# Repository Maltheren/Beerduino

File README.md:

# Beerduino
A functional arduino uno with a build in bottle opener.

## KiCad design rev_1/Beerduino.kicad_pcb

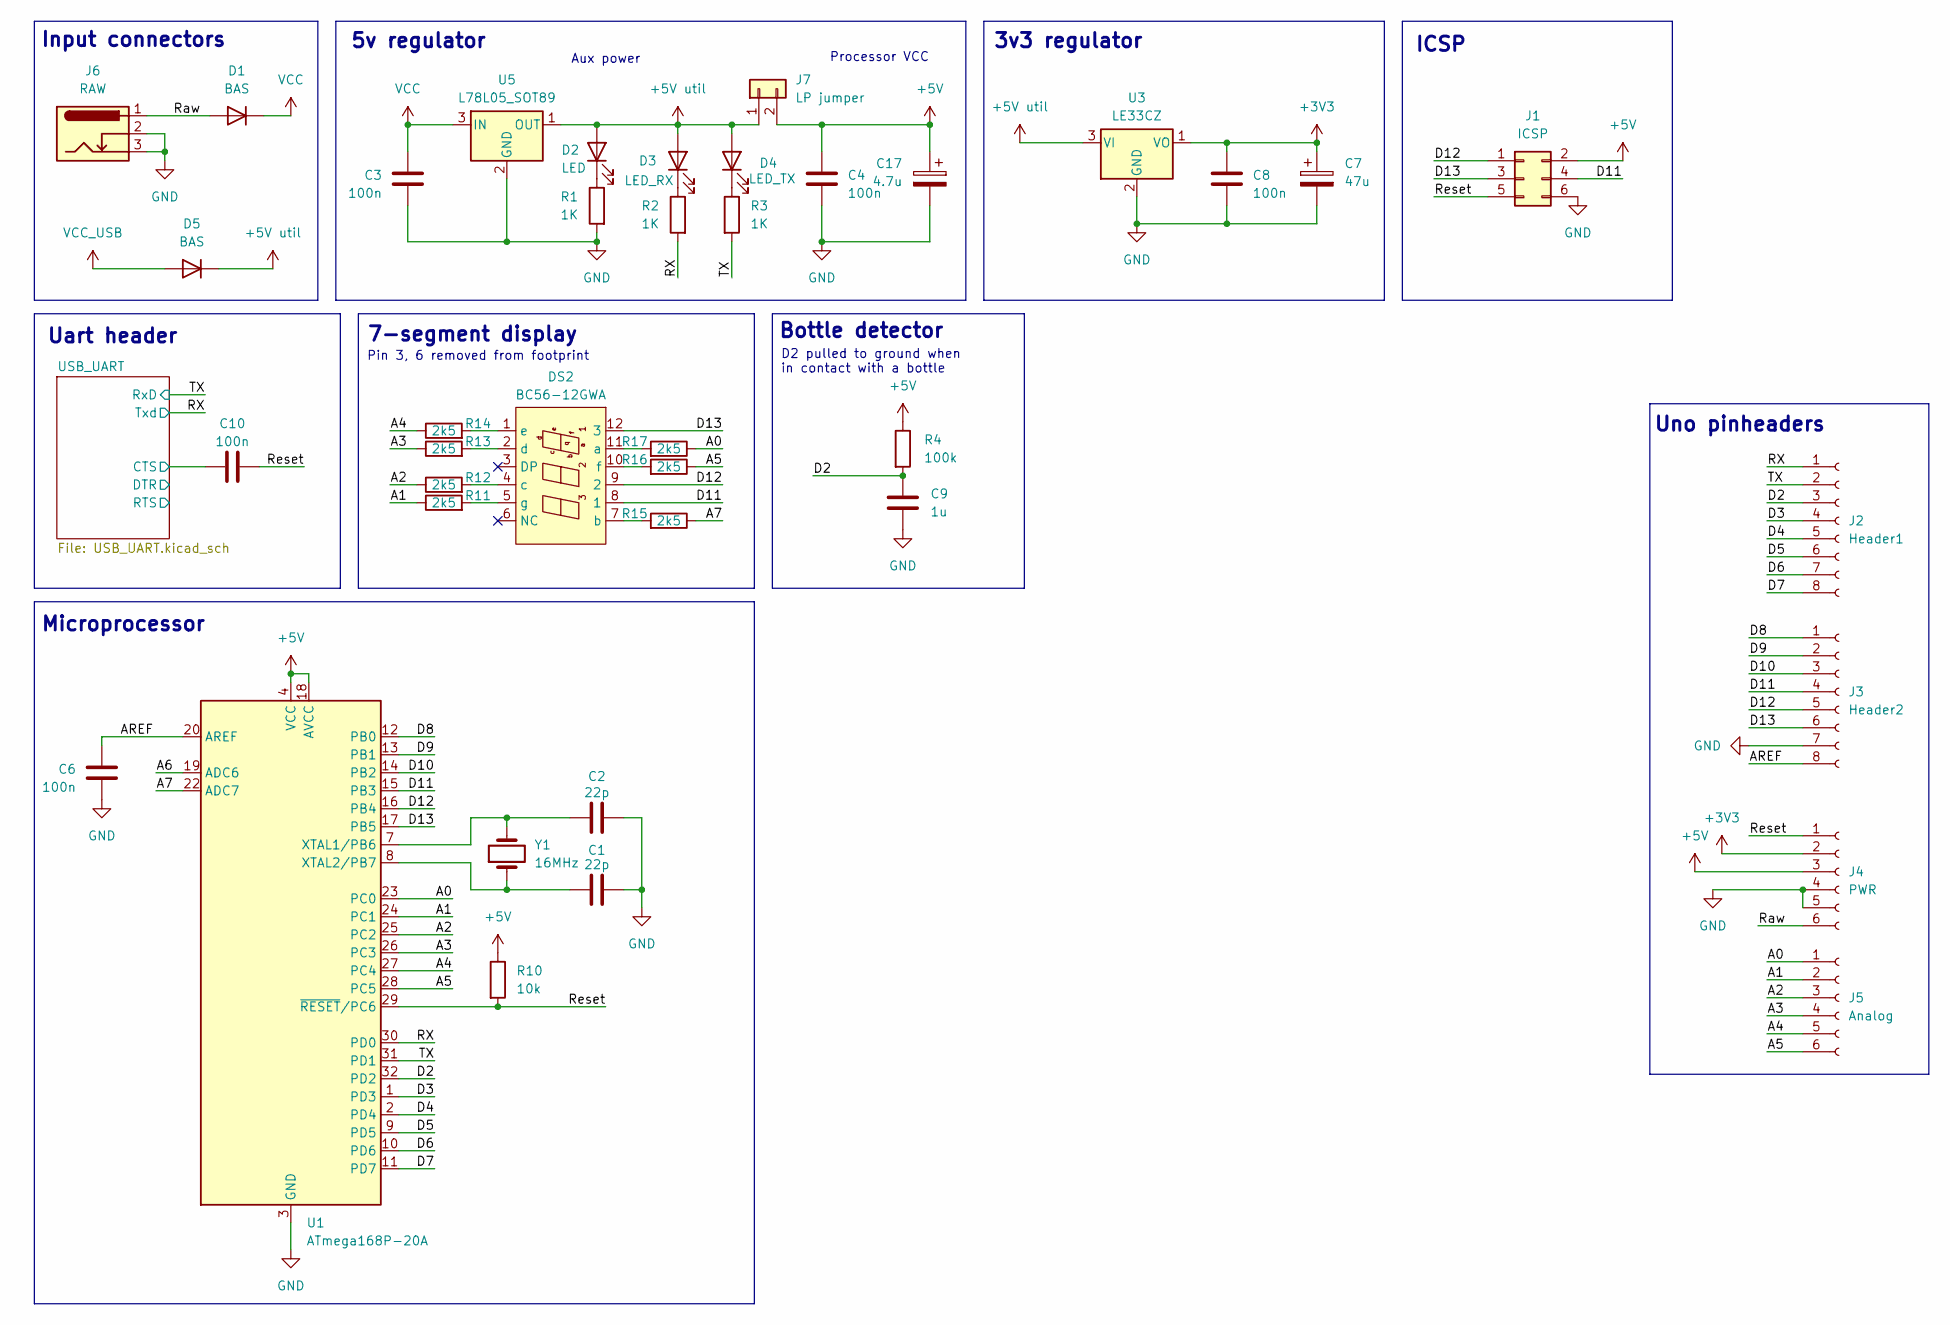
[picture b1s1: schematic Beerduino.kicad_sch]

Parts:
C1, C2: 22p; C_0603_1608Metric_Pad1.08x0.95mm_HandSolder
C3, C4, C6, C8, C10: 100n; C_0603_1608Metric_Pad1.08x0.95mm_HandSolder
C7: 47u; CP_Radial_D5.0mm_P2.50mm
C9: 1u; C_0603_1608Metric_Pad1.08x0.95mm_HandSolder
C17: 4.7u; CP_EIA-3528-15_AVX-H_HandSolder
D1, D5: BAS; D_SOD-323_HandSoldering
D2: LED; LED_0805_2012Metric_Pad1.15x1.40mm_HandSolder
D3: LED_RX; LED_0805_2012Metric_Pad1.15x1.40mm_HandSolder
D4: LED_TX; LED_0805_2012Metric_Pad1.15x1.40mm_HandSolder
DS2: BC56-12GWA; 3digit
J1: ICSP; PinHeader_2x03_P2.54mm_Vertical
J2: Header1; PinSocket_1x08_P2.54mm_Vertical
J3: Header2; PinSocket_1x08_P2.54mm_Vertical
J4: PWR; PinHeader_1x06_P2.54mm_Vertical
J5: Analog; PinHeader_1x06_P2.54mm_Vertical
J6: RAW; BarrelJack_Horizontal
J7: LP jumper; PinHeader_1x02_P2.54mm_Vertical
R1, R2, R3: 1K; R_0603_1608Metric_Pad0.98x0.95mm_HandSolder
R4: 100k; R_0603_1608Metric_Pad0.98x0.95mm_HandSolder
R10: 10k; R_0603_1608Metric_Pad0.98x0.95mm_HandSolder
R11, R12, R13, R14, R15, R16, R17: 2k5; R_0603_1608Metric_Pad0.98x0.95mm_HandSolder
U1: ATmega168P-20A; TQFP-32_7x7mm_P0.8mm
U3: LE33CZ; TO-92_HandSolder
U5: L78L05_SOT89; SOT-89-3
Y1: 16MHz; Crystal_SMD_HC49-SD

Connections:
+3V3: C7.1, C8.1, J4.2, U3.1 (VO)
+5V: C4.1, C17.1, J1.2, J4.3, J7.2, R4.1, R10.1, U1.4 (VCC), U1.6 (VCC), U1.18 (AVCC)
+5V util: D2.2 (A), D3.2 (A), D4.2 (A), D5.1 (K), J7.1, U3.3 (VI), U5.1 (OUT)
/A0: J5.1, R17.1, U1.23 (PC0)
/A1: J5.2, R11.1, U1.24 (PC1)
/A2: J5.3, R12.1, U1.25 (PC2)
/A3: J5.4, R13.1, U1.26 (PC3)
/A4: J5.5, R14.1, U1.27 (PC4)
/A5: J5.6, R16.1, U1.28 (PC5)
/A6: U1.19 (ADC6)
/A7: R15.1, U1.22 (ADC7)
/AREF: C6.1, J3.8, U1.20 (AREF)
/D2: C9.1, J2.3, R4.2, U1.32 (PD2)
/D3: J2.4, U1.1 (PD3)
/D4: J2.5, U1.2 (PD4)
/D5: J2.6, U1.9 (PD5)
/D6: J2.7, U1.10 (PD6)
/D7: J2.8, U1.11 (PD7)
/D8: J3.1, U1.12 (PB0)
/D9: J3.2, U1.13 (PB1)
/D10: J3.3, U1.14 (PB2)
/D11: DS2.8 (1), J1.4, J3.4, U1.15 (PB3)
/D12: DS2.9 (2), J1.1, J3.5, U1.16 (PB4)
/D13: DS2.12 (3), J1.3, J3.6, U1.17 (PB5)
/RX: J2.1, R2.2, U1.30 (PD0); also elsewhere on the board
/Raw: D1.2 (A), J4.6, J6.1
/Reset: C10.1, J1.5, J4.1, R10.2, U1.29 (~RESET/PC6)
/TX: J2.2, R3.2, U1.31 (PD1); also elsewhere on the board
/USB_UART/CTS: C10.2; also elsewhere on the board
GND: C1.2, C2.2, C3.2, C4.2, C6.2, C7.2, C8.2, C9.2, C17.2, J1.6, J3.7, J4.4, J4.5, J6.2, J6.3, R1.2, U1.3 (GND), U1.5 (GND), U1.21 (GND), U3.2 (GND), U5.2 (GND); also elsewhere on the board
unnamed: D2.1 (K), R1.1
unnamed: D3.1 (K), R2.1
unnamed: D4.1 (K), R3.1
unnamed: DS2.11 (a), R17.2
unnamed: DS2.7 (b), R15.2
unnamed: DS2.4 (c), R12.2
unnamed: DS2.2 (d), R13.2
unnamed: DS2.1 (e), R14.2
unnamed: DS2.10 (f), R16.2
unnamed: DS2.5 (g), R11.2
unnamed: C2.1, U1.7 (XTAL1/PB6), Y1.2
unnamed: C1.1, U1.8 (XTAL2/PB7), Y1.1
VCC: C3.1, D1.1 (K), U5.3 (IN)
VCC_USB: D5.2 (A); also elsewhere on the board

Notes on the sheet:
Aux power
Pin 3, 6 removed from footprint
Microprocessor
3v3 regulator
Uart header
Bottle detector
5v regulator
ICSP
Uno pinheaders
Processor VCC
7-segment display
Input connectors
D2 pulled to ground when in contact with a bottle

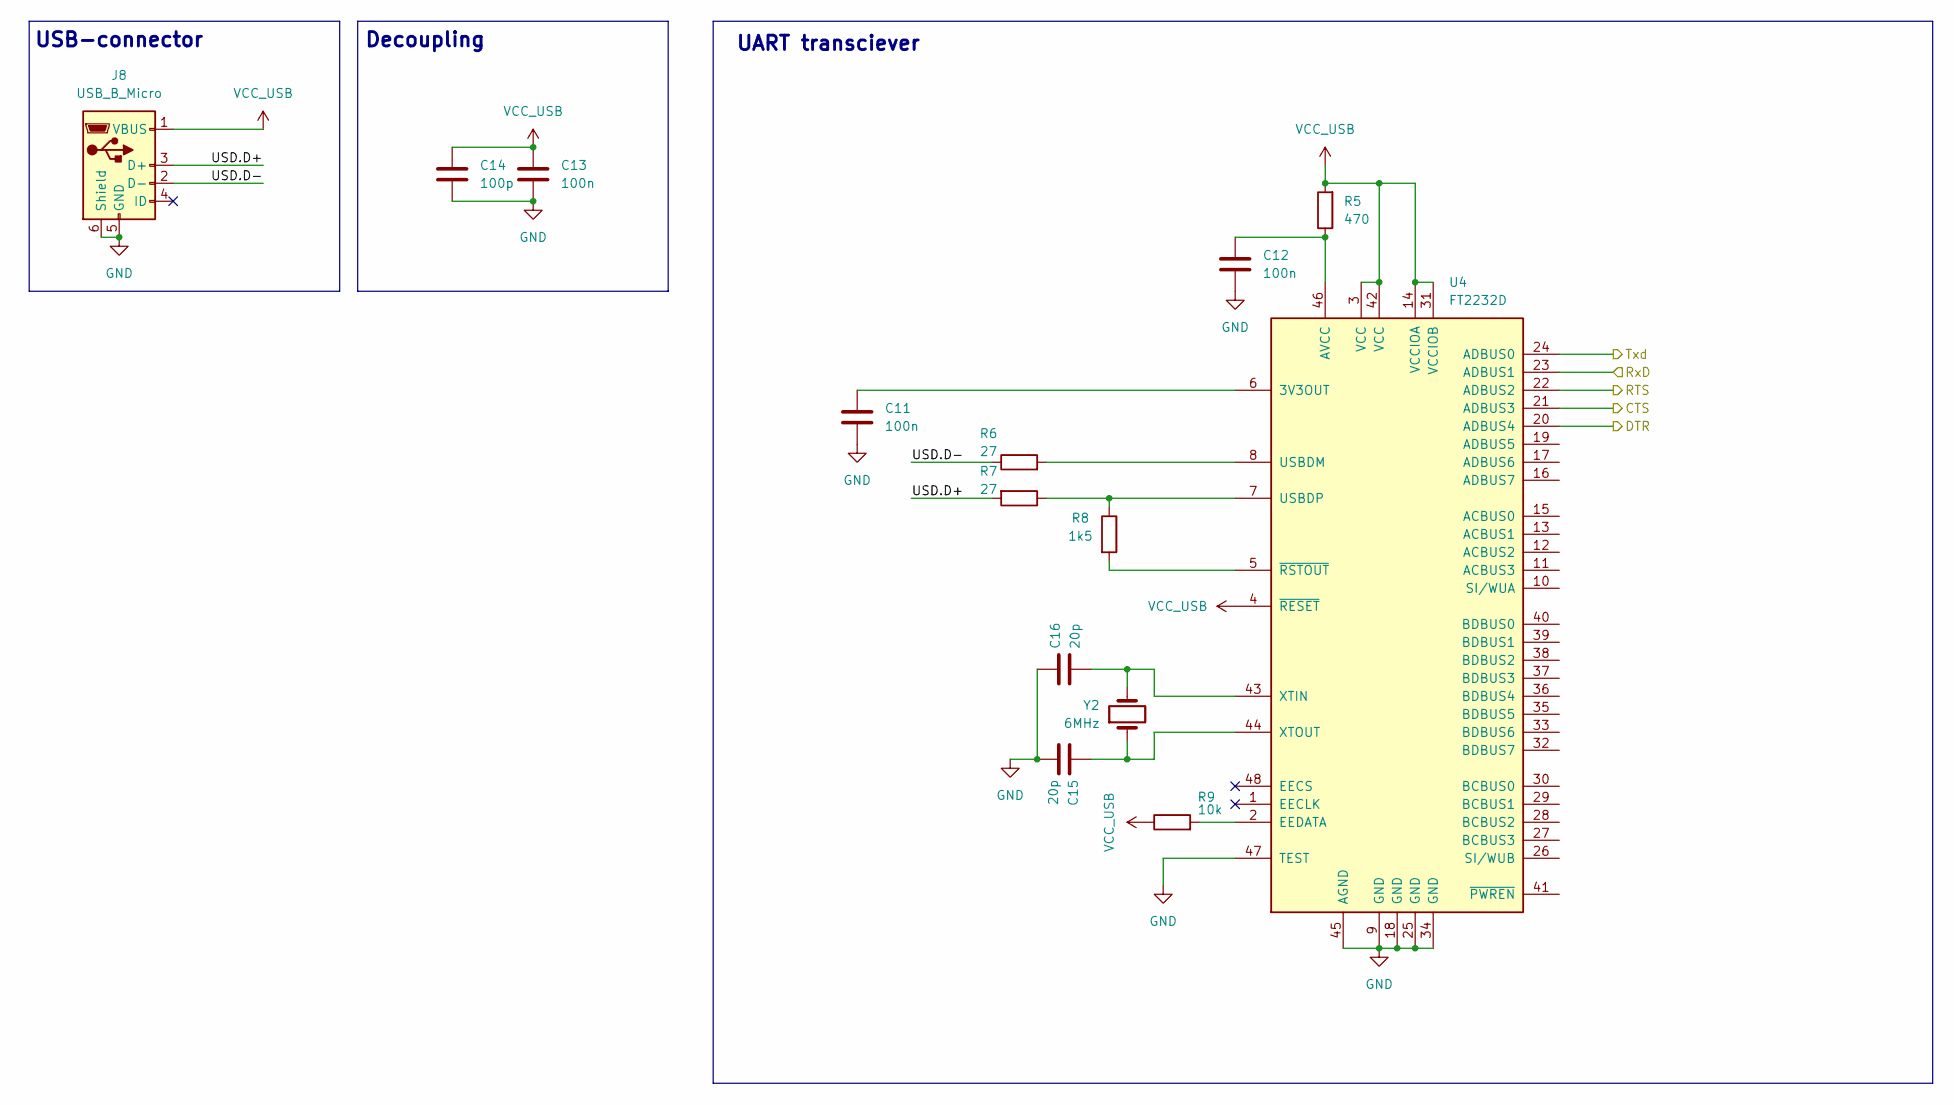
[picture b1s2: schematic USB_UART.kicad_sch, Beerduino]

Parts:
C11, C12, C13: 100n; C_0603_1608Metric_Pad1.08x0.95mm_HandSolder
C14: 100p; C_0603_1608Metric_Pad1.08x0.95mm_HandSolder
C15, C16: 20p; C_0603_1608Metric
J8: USB_B_Micro; USB_Micro-B_Wuerth_629105150521_CircularHoles
R5: 470; C_0603_1608Metric_Pad1.08x0.95mm_HandSolder
R6, R7: 27; R_0603_1608Metric_Pad0.98x0.95mm_HandSolder
R8: 1k5; R_0603_1608Metric_Pad0.98x0.95mm_HandSolder
R9: 10k; R_0603_1608Metric_Pad0.98x0.95mm_HandSolder
U4: FT2232D; LQFP-48_7x7mm_P0.5mm
Y2: 6MHz; Crystal_SMD_HC49-SD

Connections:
/RX: U4.24 (ADBUS0); also elsewhere on the board
/TX: U4.23 (ADBUS1); also elsewhere on the board
/USB_UART/CTS: U4.21 (ADBUS3); also elsewhere on the board
/USB_UART/DTR: U4.20 (ADBUS4)
/USB_UART/RTS: U4.22 (ADBUS2)
/USB_UART/USD.D+: J8.3 (D+), R7.2
/USB_UART/USD.D-: J8.2 (D-), R6.1
GND: C11.2, C12.2, C13.2, C14.2, C15.1, C16.2, J8.5 (GND), J8.6 (Shield), U4.9 (GND), U4.18 (GND), U4.25 (GND), U4.34 (GND), U4.45 (AGND), U4.47 (TEST); also elsewhere on the board
unnamed: C11.1, U4.6 (3V3OUT)
unnamed: C12.1, R5.1, U4.46 (AVCC)
unnamed: R9.2, U4.2 (EEDATA)
unnamed: R6.2, U4.8 (USBDM)
unnamed: R7.1, R8.1, U4.7 (USBDP)
unnamed: C16.1, U4.43 (XTIN), Y2.2
unnamed: C15.2, U4.44 (XTOUT), Y2.1
unnamed: R8.2, U4.5 (~RSTOUT)
VCC_USB: C13.1, C14.1, J8.1 (VBUS), R5.2, R9.1, U4.3 (VCC), U4.4 (~RESET), U4.14 (VCCIOA), U4.31 (VCCIOB), U4.42 (VCC); also elsewhere on the board

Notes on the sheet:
Decoupling
UART transciever
USB-connector

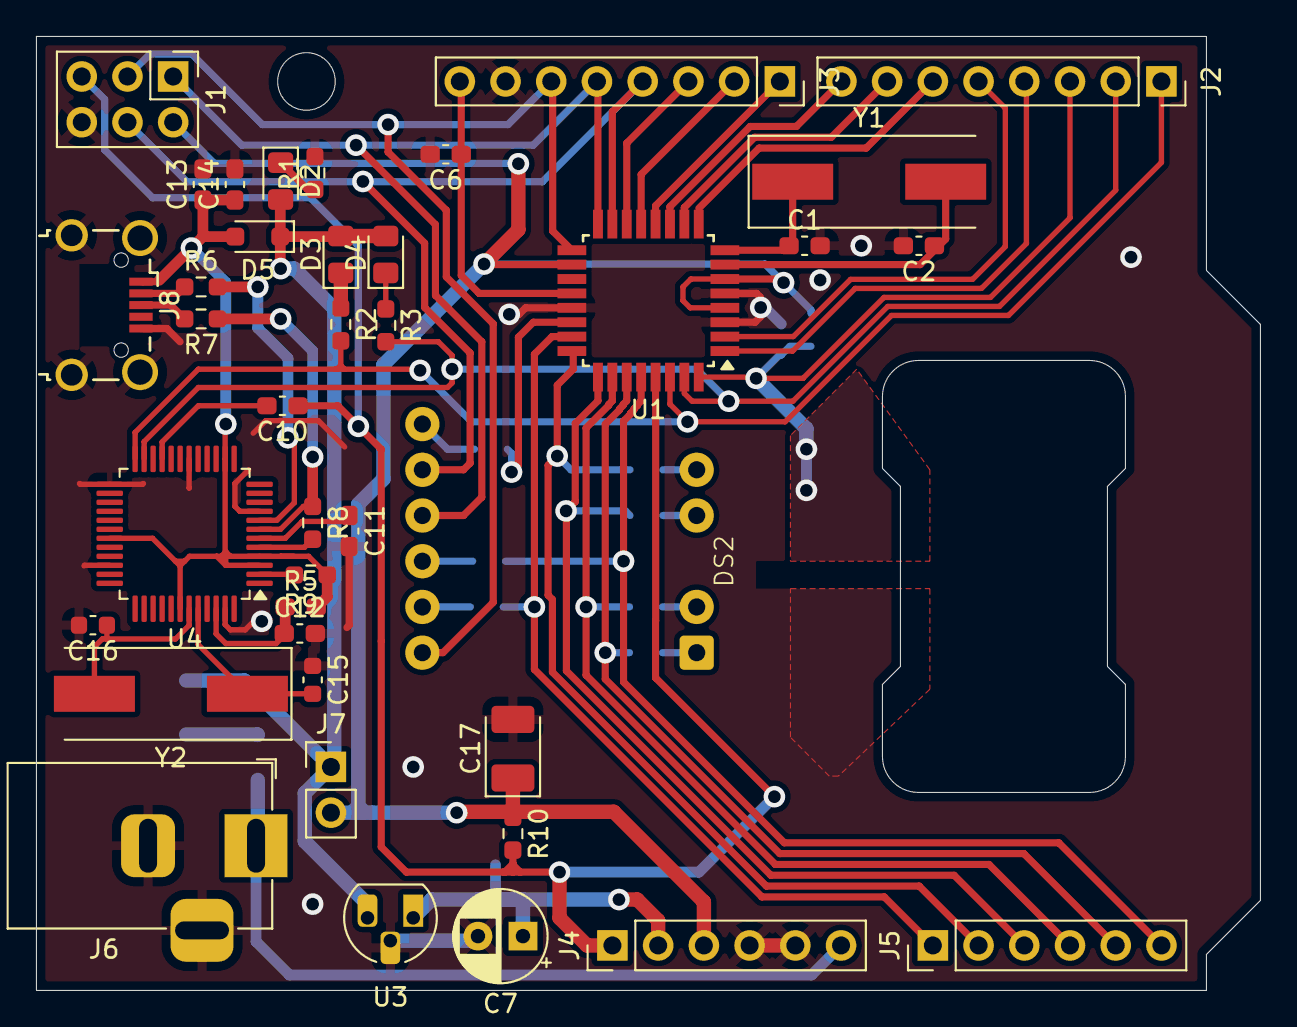
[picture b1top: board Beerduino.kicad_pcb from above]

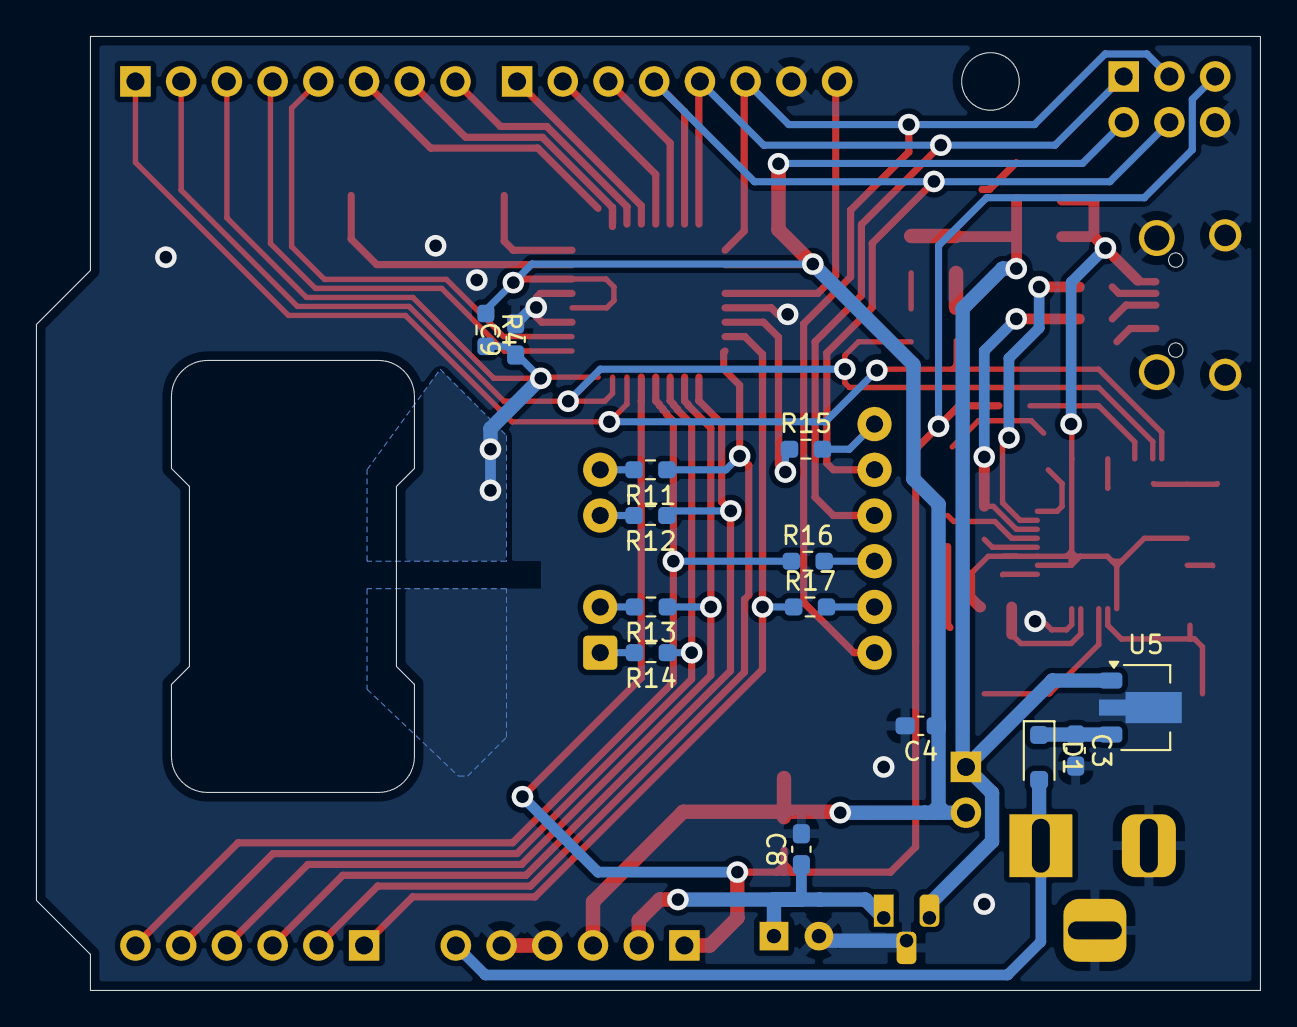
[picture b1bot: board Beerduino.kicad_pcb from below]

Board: 2 copper layers, 68.0 x 53.0 mm, 53 parts (14 on the bottom side), 53 nets.

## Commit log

2025-07-03 Update license.md
    Tried to make the license look a bit nicer, for the memes ofc
2025-07-03 rev1 initial
2025-07-03 documentation
2025-07-05 Initial rev2
